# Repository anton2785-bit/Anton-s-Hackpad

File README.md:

# Anton's Hackpad

---

## Bill of Materials (BOM)

### Standard Parts

* MX‑style mechanical switches (**8x**) ( preferebly red or black )
* Blank DSA keycaps – **White** (**8x**)
* Rotary encoder EC11E 
* XIAO RP2040-dip
* SK6812 MINI‑E (**3x**)
* M3 × 16 mm screws (**4x**)
* M3 heat‑set inserts (**4x**)

---

### Other non standard ( project specific ) parts

* Custom PCB                         
*  
* Custom schematic
* 
*  3D‑printed case (top & bottom)
*  

---

## Case & Mounting

* The case is **fully 3D‑printed** 
* Heat‑set inserts are installed into the case for durability
* PCB is mounted directly to the case 

Ensure heat‑set inserts are installed carefully using a soldering iron tip sized for M3 inserts.

---

## Assembly Notes

1. Solder all components to the PCB
2. Place the PCB in the case and screw the top plate
3. Attach keycaps 

---

## Firmware

* I used KMK for this project, but ill improve it when i get the hackpad
  
---

Perfect for:

* Coding shortcuts
* CAD 
* Learning keyboard firmware

---

## Credits

Designed and built by *(Anton/ Anton-2785-bit)*
Inspired by open‑source mechanical keyboard and hackpad communities (https://blueprint.hackclub.com/home).

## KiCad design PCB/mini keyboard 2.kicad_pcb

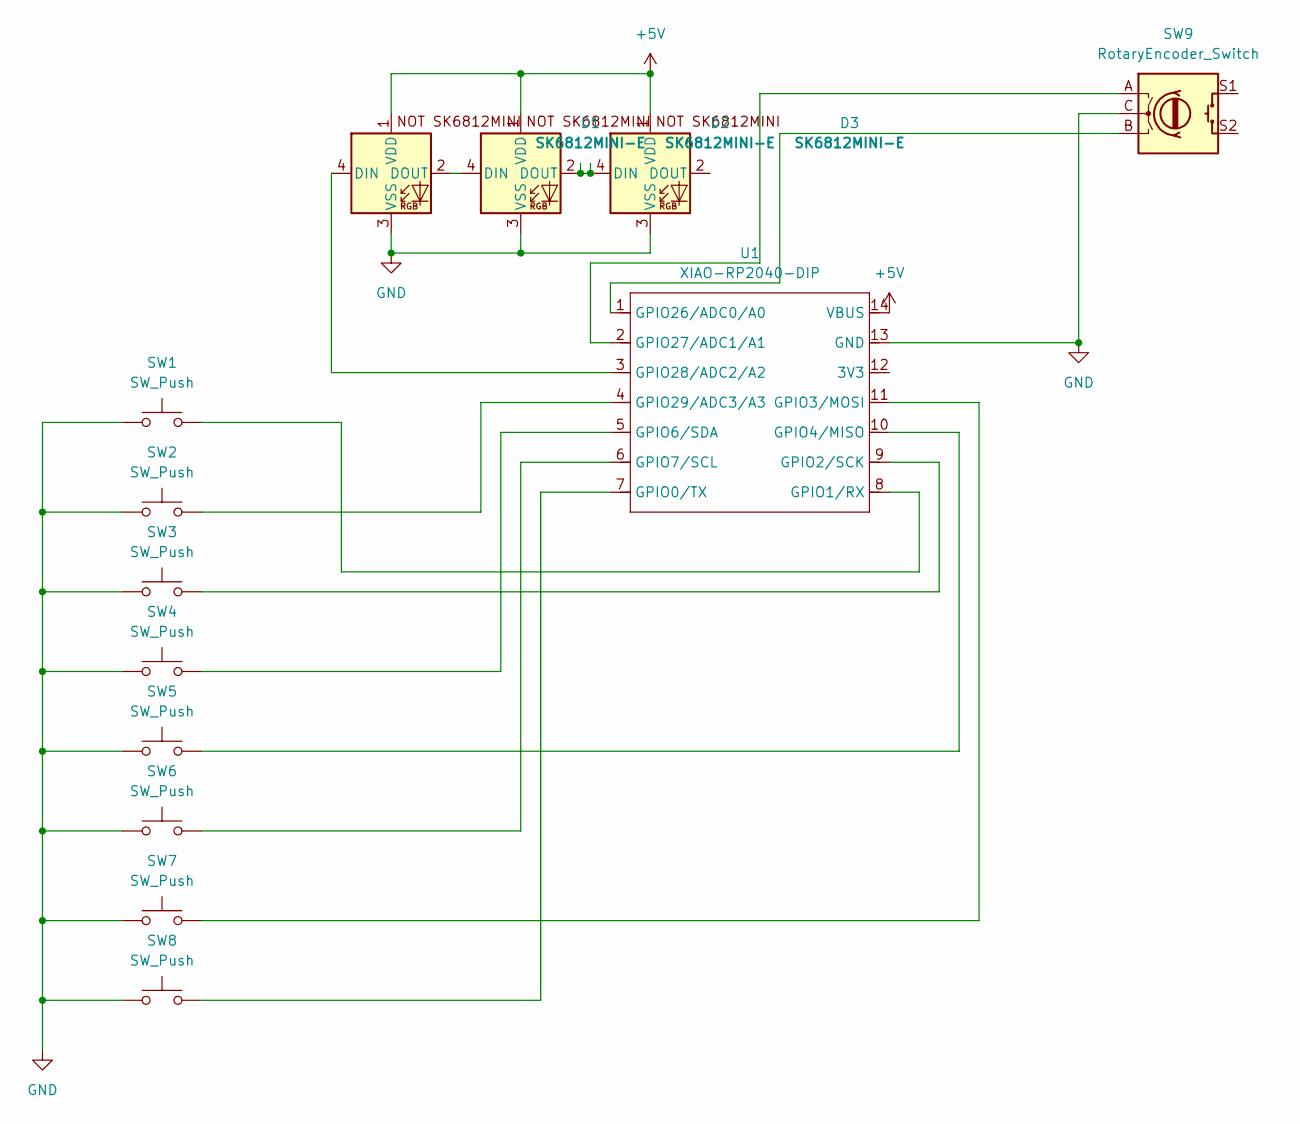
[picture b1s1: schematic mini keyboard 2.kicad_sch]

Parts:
D1, D2, D3: SK6812MINI-E; MX_SK6812MINI-E_REV
SW1, SW2, SW3, SW4, SW5, SW6, SW7, SW8: SW_Push; SW_Cherry_MX_1.00u_PCB
SW9: RotaryEncoder_Switch; RotaryEncoder_Alps_EC11E-Switch_Vertical_H20mm
U1: XIAO-RP2040-DIP

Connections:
+5V: D1.1 (VDD), D2.1 (VDD), D3.1 (VDD), U1.14 (VBUS)
GND: D1.3 (VSS), D2.3 (VSS), D3.3 (VSS), SW1.1, SW2.1, SW3.1, SW4.1, SW5.1, SW6.1, SW7.1, SW8.1, SW9.C, U1.13 (GND)
unnamed: D1.4 (DIN), U1.3 (GPIO28/ADC2/A2)
unnamed: D1.2 (DOUT), D2.4 (DIN)
unnamed: D2.2 (DOUT), D3.4 (DIN)
unnamed: SW8.2, U1.7 (GPIO0/TX)
unnamed: SW1.2, U1.8 (GPIO1/RX)
unnamed: SW3.2, U1.9 (GPIO2/SCK)
unnamed: SW7.2, U1.11 (GPIO3/MOSI)
unnamed: SW5.2, U1.10 (GPIO4/MISO)
unnamed: SW4.2, U1.5 (GPIO6/SDA)
unnamed: SW6.2, U1.6 (GPIO7/SCL)
unnamed: SW9.B, U1.1 (GPIO26/ADC0/A0)
unnamed: SW9.A, U1.2 (GPIO27/ADC1/A1)
unnamed: SW2.2, U1.4 (GPIO29/ADC3/A3)

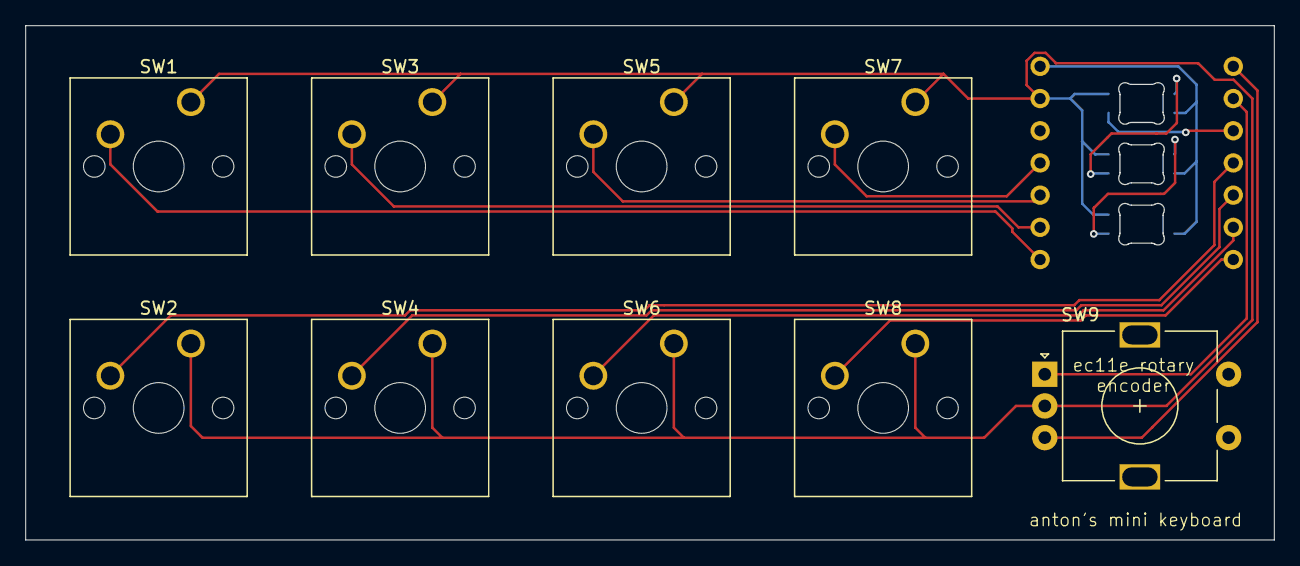
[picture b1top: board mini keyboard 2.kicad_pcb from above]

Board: 2 copper layers, 98.4 x 40.5 mm, 13 parts (1 on the bottom side), 15 nets.

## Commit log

2026-01-25 Update files
2026-01-26 Revise README for Mini Keyboard project
    Updated the README to reflect the new project details for a mini keyboard, including specifications, assembly notes, and firmware compatibility.
2026-01-27 Update README by removing sections
    Removed overview and repository contents sections from README.
